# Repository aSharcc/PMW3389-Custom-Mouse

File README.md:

https://github.com/user-attachments/assets/145927b7-b68a-468a-8b0a-571980a8af83

# PMW3389 Custom DIY Mouse

A fully custom gaming mouse using a PixArt PMW3389.

2 versions. 3.3V/8MHz Arduino Pro Micro (ATmega32U4) and Seeed Studio XIAO ESP32C3.

I also intend for this mouse to be easily repairable.

Be sure to read [BOM.md](docs/BOM.md)

### Thanks to PCBWay for collaborating on this project
- Provided PCBs for v2 and v3 prototyping
- High quality
- Manufactured and shipped quickly
- No faults
- Fast reviewing

## Key Features

- High performance sensor: 16,000 DPI via PixArt PMW3389
- Modular and Repairable
	- Hotswap Main Switches: Uses Mill-Max 3305 so can be replaced with no soldering
	- Replaceable MCU: Mounted using through-hole pin headers
- Wireless and wired versions.
- Sensor communication through SPI

## Version Comparison

|Features|v2 (Wired)|v3 (Wireless)|
|---|---|---|
|MCU|3.3V/8MHz Arduino Pro Micro (ATmega32U4)|Seeed Studio XIAO ESP32C3|
|Connectivity|Micro-USB|Bluetooth / 2.4GHz Wireless|
|Power Source|Micro-USB|LiPo Battery|
|Production Files|[Files v2](https://github.com/aSharcc/PMW3389-Custom-Mouse/releases/tag/2.0)|[Files v3](https://github.com/aSharcc/PMW3389-Custom-Mouse/releases/tag/3.0)|
### v2

<picture>
	
</picture>

### v3

## How To Use

**DETAILED INSTRUCTIONS and BOM [HERE](docs/BOM.md)**

1. Order the PCB from a PCB manufacturer (e.g. JLCPCB) with files from specific release.
2. Either:
   - Order PCBA for the SMD components, or
   - Purchase the SMD components and hand solder them. 
3. Purchase the components listed in the BOM that are not included in PCBA.
4. Hand solder/install the components not included in PCBA.
5. Download the PMW3389 library.
	- For Wired: [Arduino PMW3389 Library](Firmware/Arduino/README.md) for instructions.
	- For Wireless: [ESP32 PMW3389 Library](Firmware/ESP32/README.md) for instructions.
6. Download Firmware
	- For Wired: [Arduino Firmware](https://github.com/aSharcc/PMW3389-Custom-Mouse/releases/download/2.0/Mouse.Firmware.ino)
	- For Wireless: [ESP32 Firmware](https://github.com/aSharcc/PMW3389-Custom-Mouse/releases/download/3.0/BasicMouse.ino)
7. Flash the firmware to the MCU.
8. Download and print the 3D models.
	- For Wired: [Top](https://github.com/aSharcc/PMW3389-Custom-Mouse/releases/download/2.0/Mouse.Shell.top.gcode.3mf) + [Bottom](https://github.com/aSharcc/PMW3389-Custom-Mouse/releases/download/2.0/Mouse.Shell.bottom.gcode.3mf) + [Scroll](https://github.com/aSharcc/PMW3389-Custom-Mouse/releases/download/2.0/Mouse.Shell.knob.gcode.3mf)
	- For Wireless: [Top](https://github.com/aSharcc/PMW3389-Custom-Mouse/releases/download/3.0/Mouse.Shell.v3.top.gcode.3mf) + [Bottom](https://github.com/aSharcc/PMW3389-Custom-Mouse/releases/download/3.0/Mouse.Shell.v3.bottom.gcode.3mf) + [Scroll](https://github.com/aSharcc/PMW3389-Custom-Mouse/releases/download/3.0/Mouse.Shell.v3.knob.gcode.3mf)
9. Add threaded heat inserts to the shell.
10. **For Wireless Only**:
	- **Not Completed** Will include power switch and battery stuff.
11. Assemble the mouse.

## Components

- Sensor: PixArt PMW3389 and LM19-LCT Lens

- MCU: 3.3V/8MHz Arduino Pro Micro (ATmega32U4) or Seeed Studio XIAO ESP32C3 

- Switches: 2 x Huano Blue Shell Pink Dot Mouse Switches  
 
- Scroll Wheel: Rotary Encoder w/Switch (EC11) 

- Hot Swap Socket for Switches: 6 x Mill-Max 3305

- SMD Components (0805)
	- 1 x 13 ohm resistor
	- 1 x 10k ohm resistor
	- 5 x 0.1uF capacitor
	- 3 x 10uF capacitor
	- 1 x 4.7uF capacitor
	- 1 x XC6206-1.8V LDO

- PTFE Mouse Skates

- Micro USB Cable for v2 or USB-C cable for v3 charging

- Mounting Hardware
	- 7 x Heat Inserts M2 x 3 x 3.2
	- 3 x M2 x 4 Screw
	- 4 x M2 x 7 Screw

- **FOR V3 ONLY**:
	- 500mAh battery with JST connector
	- SPDT / 1P2T PCB slide switch
	- 10cm male to female USB-C cable	

## Pinout

|Component|Usage|v2 (3.3v/8MHz Pro Micro)|v3 (XIAO ESP32)|
|---|---|---|---|
|**PMW3389**|NCS|D10|D3|
||MOSI|D16 (MOSI)|D10 (MOSI)|
||MISO|D14 (MISO)|D9 (MISO)|
||SCLK|D15 (SCLK)|D8 (SCLK)|
||MOT|D2 (INT 1)|D4|
|**Rotary Encoder w/Switch**|Rotary Encoder A|D3 (INT 0)|D6|
||Rotary Encoder B|D7 (INT 6)|D0|
||Encoder Switch S2 (Middle Click)|D8|D7|
|**Switches**|Switch 1 (Left Click)|D4|D1|
||Switch 2 (Right Click)|D9|D2|

## Documentation & Credits

- [Build & Design Log](CHANGELOG.md)
- [Third-Party Credits & Libraries](CREDITS.md)
- [MIT License](LICENSE)

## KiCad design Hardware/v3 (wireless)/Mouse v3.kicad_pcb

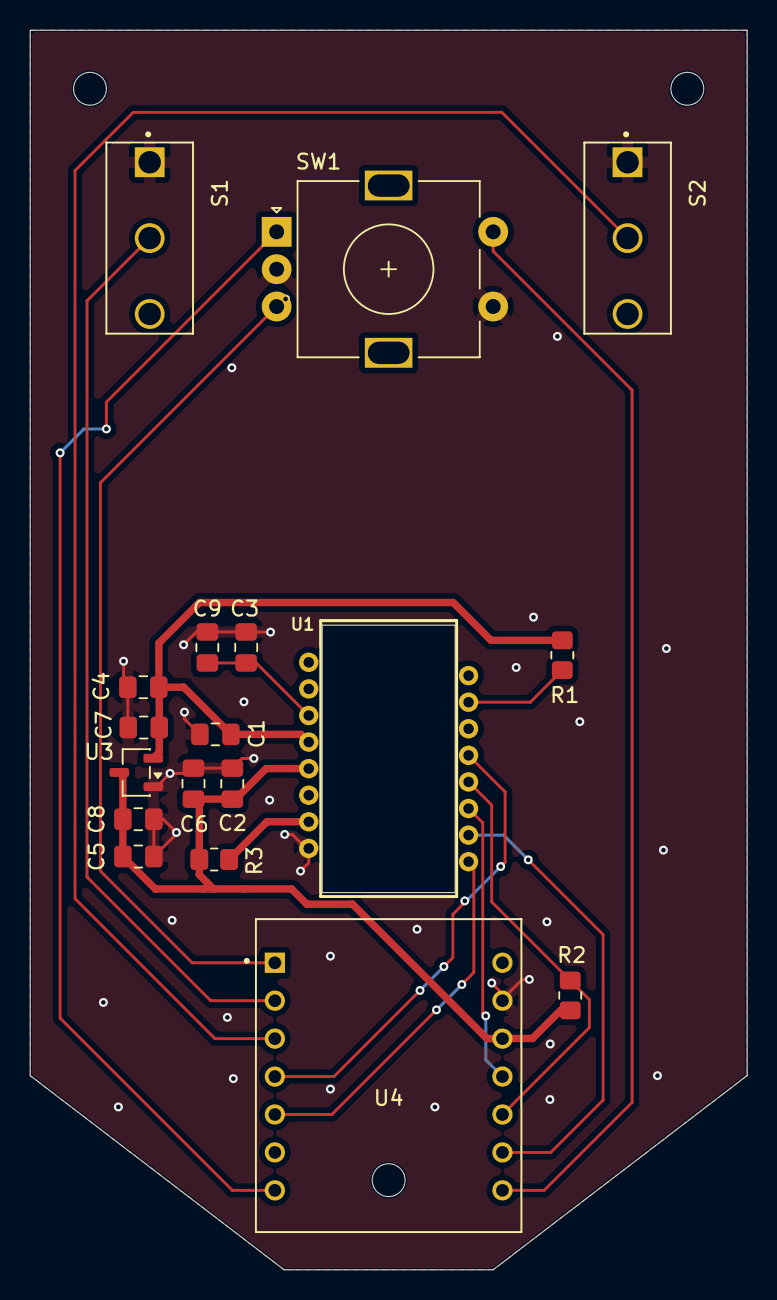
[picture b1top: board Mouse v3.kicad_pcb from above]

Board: 2 copper layers, 48.0 x 83.0 mm, 18 parts (0 on the bottom side), 16 nets.

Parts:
C1, C2, C3, C4, C5: 0.1uF; C_0805_2012Metric_Pad1.18x1.45mm_HandSolder
C6, C7, C8: 10uF; C_0805_2012Metric_Pad1.18x1.45mm_HandSolder
C9: 4.7uF; C_0805_2012Metric_Pad1.18x1.45mm_HandSolder
R1: 13Ω; R_0805_2012Metric_Pad1.20x1.40mm_HandSolder
R2, R3: 10kΩ; R_0805_2012Metric_Pad1.20x1.40mm_HandSolder
S1: Mouse Switch Left; SW_D2FC-F-7N_100M_
S2: Mouse Switch Right; SW_D2FC-F-7N_100M_
SW1: Scroll + Middle; RotaryEncoder_Alps_EC11E-Switch_Vertical_H20mm
U1: PMW3389; PMW3360
U3: XC6206-1.8V; SOT-23-3
U4: XIAO_ESP32C3; MODULE_XIAO_ESP32C3

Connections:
+1V8: C1.2, C4.1, C7.1, R1.2, U1.4 (VDD), U3.2 (VO)
+3V3: C2.2, C5.1, C6.2, C8.1, R2.1, R3.1, U1.5 (VDDIO), U3.3 (VI), U4.12 (VCC_3V3)
/Left Click: S1.2, U4.2 (D1)
/MISO: R2.2, U1.12 (MISO), U4.10 (D9)
/MOSI: U1.11 (MOSI), U4.11 (D10)
/MOT: U1.9 (MOTION), U4.5 (D4)
/Middle Click: SW1.S2, U4.8 (RX_D7)
/NCS: U1.13 (~CS), U4.4 (D3)
/Right Click: S2.2, U4.3 (D2)
/Rot A: SW1.A, U4.7 (TX_D6)
/Rot B: SW1.B, U4.1 (D0)
/SCLK: U1.10 (SCLK), U4.9 (D8)
GND: C1.1, C2.1, C3.2, C4.2, C5.2, C6.1, C7.2, C8.2, C9.2, S1.1, S2.1, SW1.C, SW1.S1, U1.8 (GND), U3.1 (GND), U4.13 (GND)
unnamed: R1.1, U1.15 (LED_P)
unnamed: C3.1, C9.1, U1.3 (VDDPIX)
unnamed: R3.2, U1.7 (~RESET)

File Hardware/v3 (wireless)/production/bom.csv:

Designator,Footprint,Quantity,Value,LCSC Part #
"C1, C2, C3, C4, C5",0805,5,0.1uF,
"C6, C7, C8",0805,3,10uF,
C9,0805,1,4.7uF,
R1,0805,1,13Ω,
"R2, R3",0805,2,10kΩ,
U3,SOT-23-3,1,XC6206-1.8V,
